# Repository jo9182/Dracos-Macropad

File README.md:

# Draco's Macropad

Whole thing together. Wasn't really sure where to find Switches for my model :(

Fun wing design on the bottom (I took way too much time making it).

Draco's Macropad! Likely for use with my wonderful soundboards.

### Inspiration

I wanted to create a macropad that allowed me to effectively spam sounds at my friends whilst in group calls. A noble cause, is it not?

### Challenges

I haven't used any of this before (save for VSCode), so... there's that. Despite the difficulty of using these initally, I actually really enjoyed the PCB making process! Fusion360 was alright, but it burnt me out a lot more than KiCAD, despite the simplicity of what I was making. 

### Specifications

Bill Of Materials: 
- 5x Cherry MX Switches
- 5x Blank DSA Keycaps
- 2x SK6812 MINI Leds
- 1x XIAO RP2040
- 4x M3x16 Bolt
- 4x M3 Heatset

Others:
- KMK Firmware
- Top Panel of Macropad.stl 
- Bottom Piece of Macropad with designs.stl

Schematic            |  PCB         |   Case
:-------------------------:|:-------------------------:|:-------------------------:|
 |   |

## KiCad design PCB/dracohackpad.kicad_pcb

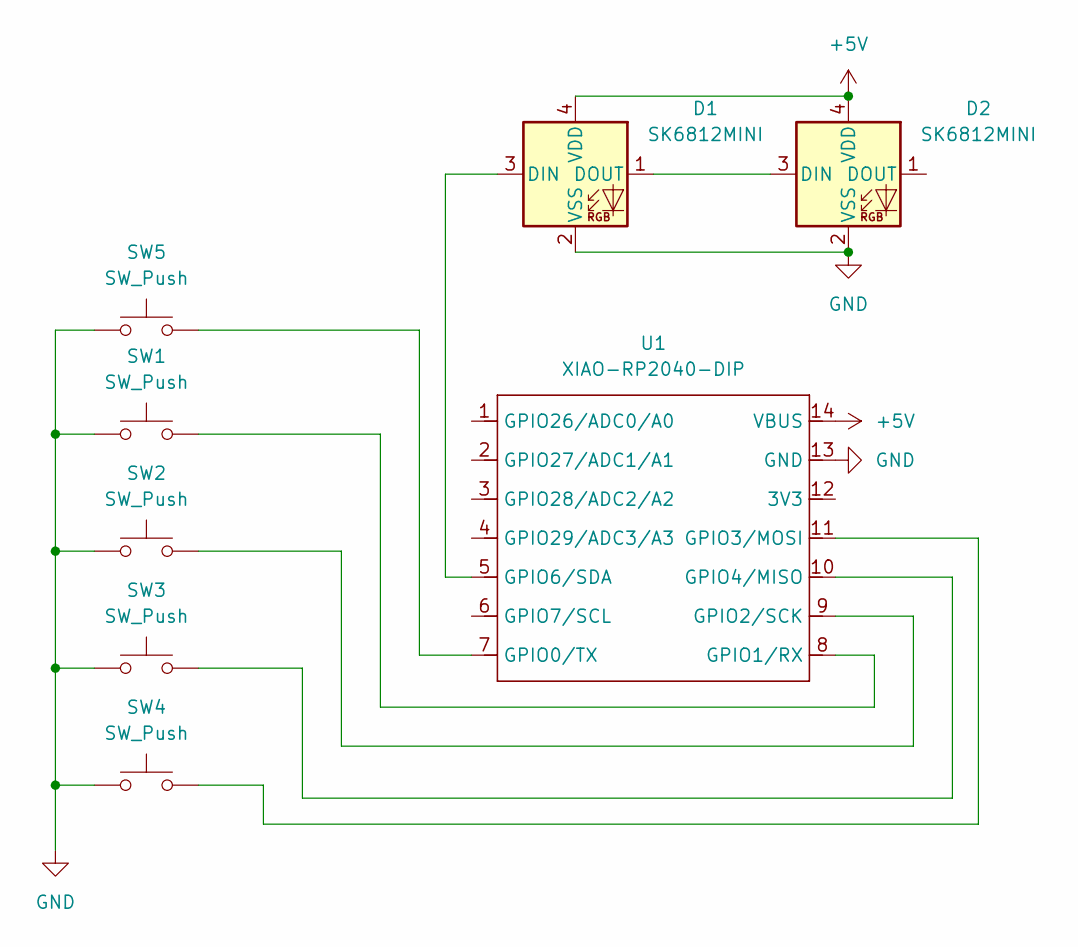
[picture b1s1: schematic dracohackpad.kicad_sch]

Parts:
D1, D2: SK6812MINI; LED_SK6812MINI_PLCC4_3.5x3.5mm_P1.75mm
SW1, SW2, SW3, SW4, SW5: SW_Push; SW_Cherry_MX_1.00u_PCB
U1: XIAO-RP2040-DIP

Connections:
+5V: D1.4 (VDD), D2.4 (VDD), U1.14 (VBUS)
GND: D1.2 (VSS), D2.2 (VSS), SW1.1, SW2.1, SW3.1, SW4.1, SW5.1, U1.13 (GND)
unnamed: D1.3 (DIN), U1.5 (GPIO6/SDA)
unnamed: D1.1 (DOUT), D2.3 (DIN)
unnamed: SW5.2, U1.7 (GPIO0/TX)
unnamed: SW1.2, U1.8 (GPIO1/RX)
unnamed: SW2.2, U1.9 (GPIO2/SCK)
unnamed: SW4.2, U1.11 (GPIO3/MOSI)
unnamed: SW3.2, U1.10 (GPIO4/MISO)

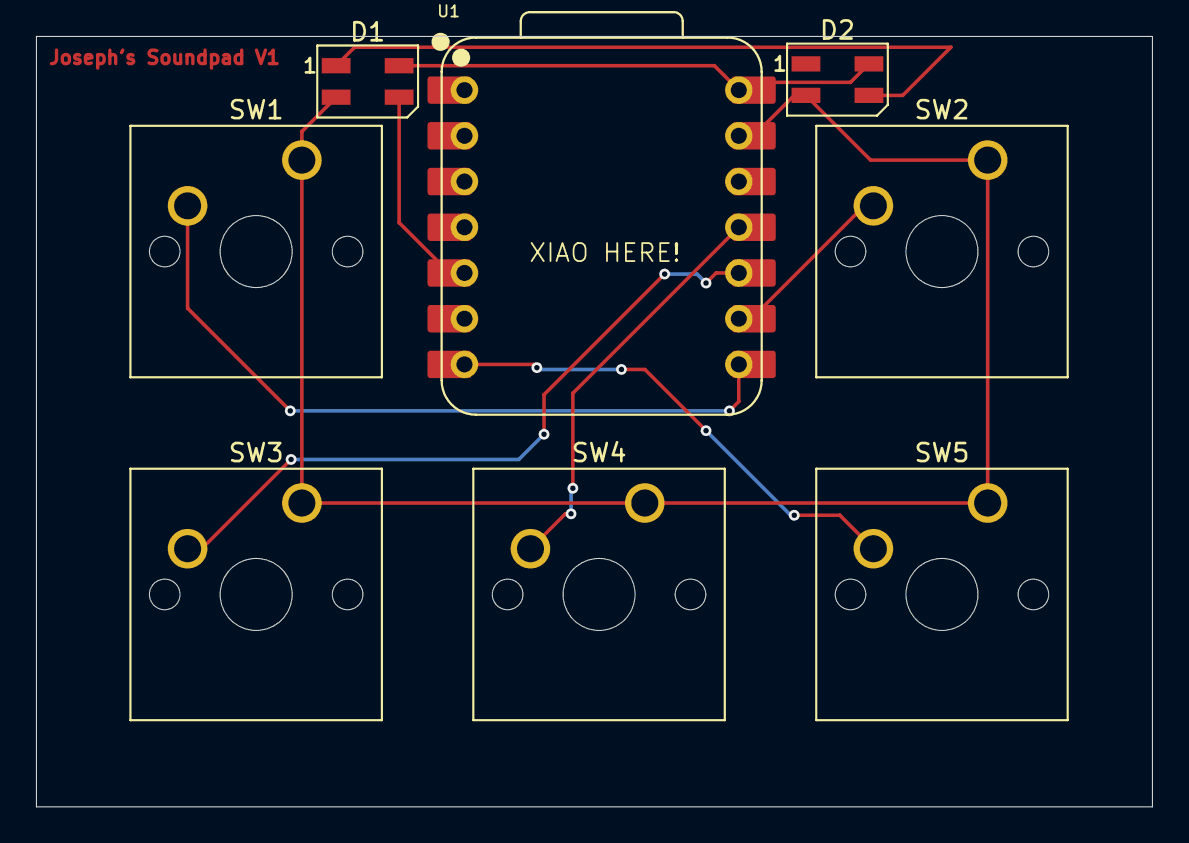
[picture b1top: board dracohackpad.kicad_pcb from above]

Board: 2 copper layers, 62.0 x 42.8 mm, 8 parts (0 on the bottom side), 9 nets.

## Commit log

2025-11-20 Making CAD directory
    making CAD directory
2025-11-20 Making Firmware directory
2025-11-20 Making PCB directory
2025-11-20 Make Production directory
2025-11-20 3d models for macropad
2025-11-23 README stuff :D
    Added all needed information (I think)
2025-11-23 firmware
    WE love kmk
2025-11-23 nvm you don't need this
2025-11-23 Slapped in how the case would fit together.
2025-11-23 Yummy PCB files...
2025-11-23 vaporize CAD/obligatorystandin.txt
2025-11-23 liquify Firmware/the.txt
2025-11-23 atomize PCB/thethe.txt
2025-11-26 Update README
    Added new screenshots
2025-11-26 Image was too big
2025-11-26 Updated 3d models
